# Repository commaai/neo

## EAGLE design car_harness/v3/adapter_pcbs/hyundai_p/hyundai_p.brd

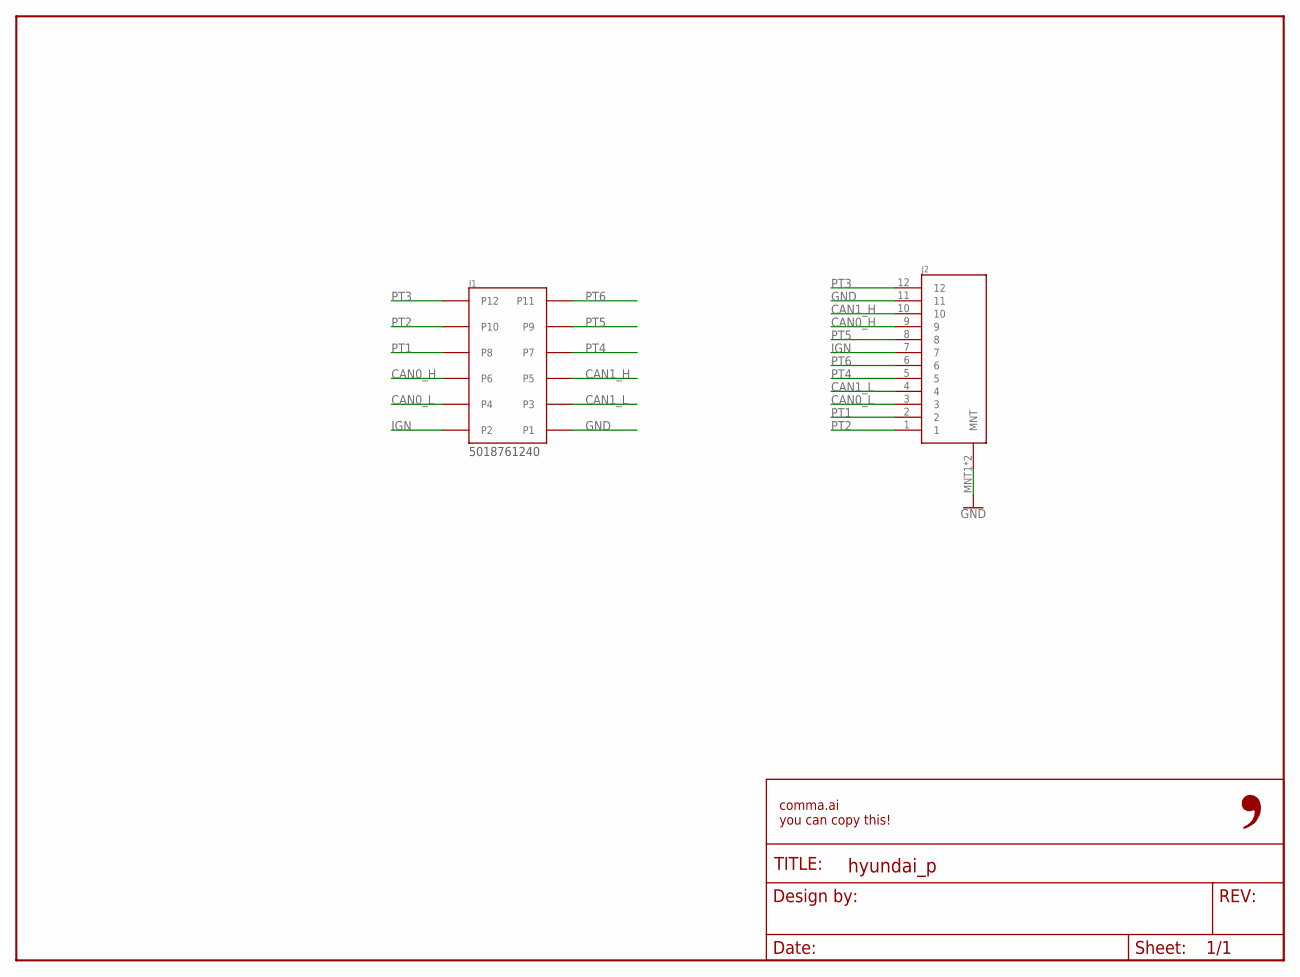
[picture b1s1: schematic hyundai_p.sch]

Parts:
FRAME1: FRAME-LETTER-OPENNO_PACKAGE; DUMMY
J1: 5018761240
J2: MG646151

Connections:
CAN0_H: J1.P6, J2.9
CAN0_L: J1.P4, J2.3
CAN1_H: J1.P5, J2.10
CAN1_L: J1.P3, J2.4
GND: J1.P1, J2.11, J2.MNT1 (MNT), J2.MNT2 (MNT)
IGN: J1.P2, J2.7
PT1: J1.P8, J2.2
PT2: J1.P10, J2.1
PT3: J1.P12, J2.12
PT4: J1.P7, J2.5
PT5: J1.P9, J2.8
PT6: J1.P11, J2.6

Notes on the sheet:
5018761240

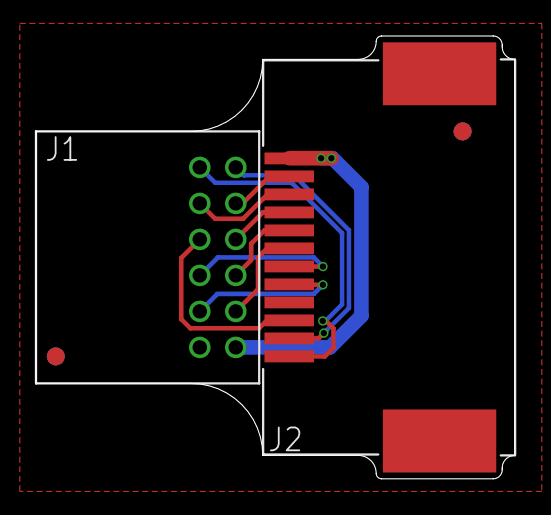
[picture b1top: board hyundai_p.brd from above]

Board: 2 copper layers, 26.6 x 24.6 mm, 6 parts (1 on the bottom side), 12 nets.

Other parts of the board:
U$1: LOGO
U$2, U$3: FIDUCIAL

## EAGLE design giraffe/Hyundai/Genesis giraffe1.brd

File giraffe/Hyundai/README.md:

thsi is test for hyundai Giraffe
the designs have not beeen tested

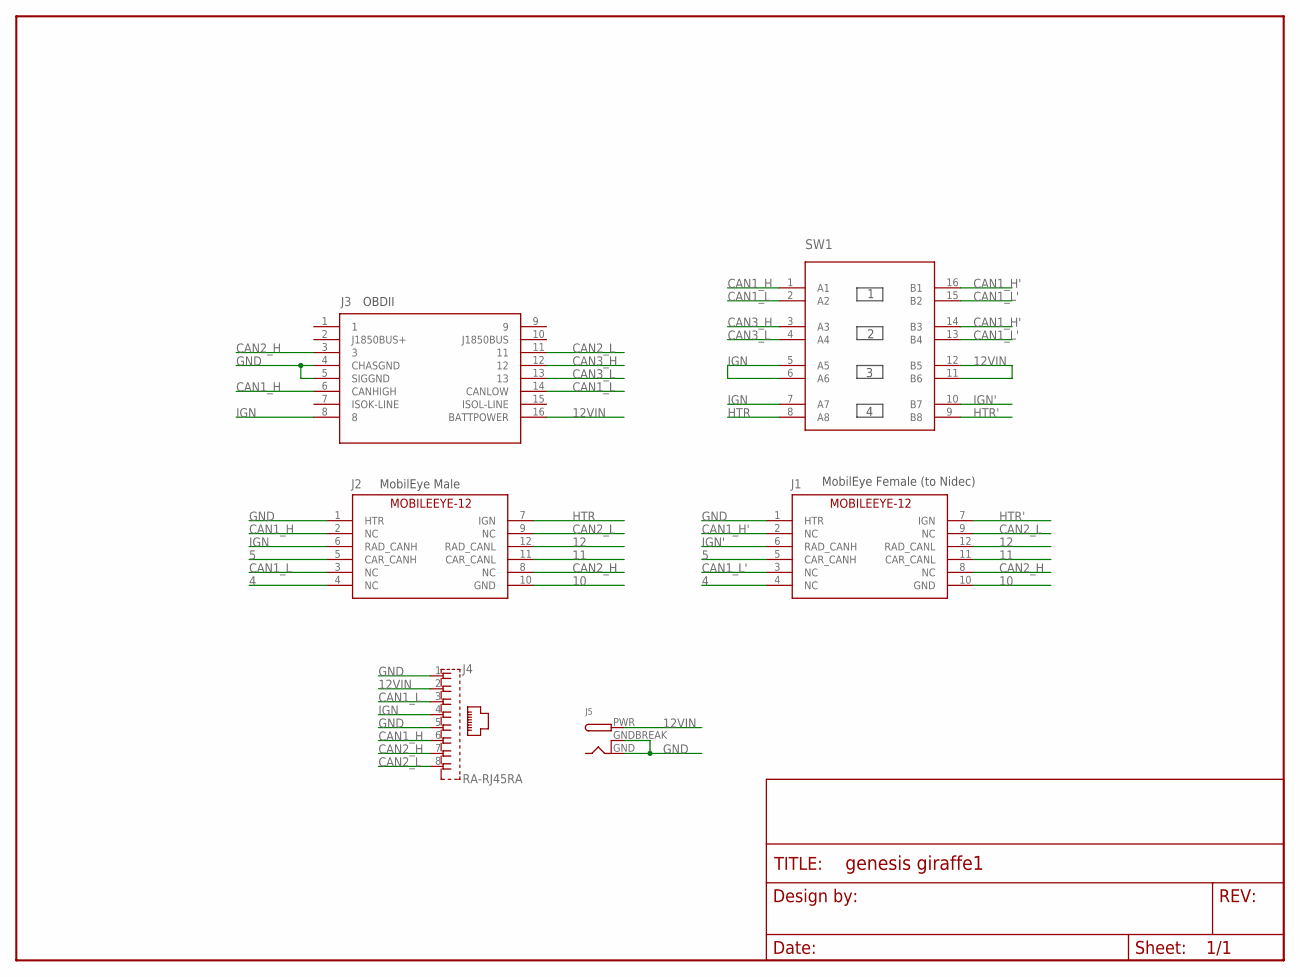
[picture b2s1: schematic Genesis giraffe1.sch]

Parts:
FRAME1: FRAME-LETTERNO_PACKAGE; DUMMY
J1: MOBILEEYE-12FEMALE; 2X6-TE-FEMALE
J2: MOBILEEYE-12MALE; 2X6-TE-RA
J3: OBDII-FEMALE-CUT; OBDII-FEMALE-MIDCUT
J4: RA-RJ45RA; RA-RJ45
J5: DCBARRELPTH; DCJACK_2MM_PTH
SW1: 4XDPSTSMT; 4-DPST

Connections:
4: J1.4 (NC), J2.4 (NC)
5: J1.5 (CAR_CANH), J2.5 (CAR_CANH)
10: J1.10 (GND), J2.10 (GND)
11: J1.11 (CAR_CANL), J2.11 (CAR_CANL)
12: J1.12 (RAD_CANL), J2.12 (RAD_CANL)
12VIN: J3.16 (BATTPOWER), J4.2, J5.PWR, SW1.11 (B6), SW1.12 (B5)
CAN1_H: J2.2 (NC), J3.6 (CANHIGH), J4.6, SW1.1 (A1)
CAN1_H': J1.2 (NC), SW1.14 (B3), SW1.16 (B1)
CAN1_L: J2.3 (NC), J3.14 (CANLOW), J4.3, SW1.2 (A2)
CAN1_L': J1.3 (NC), SW1.13 (B4), SW1.15 (B2)
CAN2_H: J1.8 (NC), J2.8 (NC), J3.3, J4.7
CAN2_L: J1.9 (NC), J2.9 (NC), J3.11, J4.8
CAN3_H: J3.12, SW1.3 (A3)
CAN3_L: J3.13, SW1.4 (A4)
GND: J1.1 (HTR), J2.1 (HTR), J3.4 (CHASGND), J3.5 (SIGGND), J4.1, J4.5, J5.GND, J5.GNDBREAK
HTR: J2.7 (IGN), SW1.8 (A8)
HTR': J1.7 (IGN), SW1.9 (B8)
IGN: J2.6 (RAD_CANH), J3.8, J4.4, SW1.5 (A5), SW1.6 (A6), SW1.7 (A7)
IGN': J1.6 (RAD_CANH), SW1.10 (B7)

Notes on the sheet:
OBDII
MobilEye Male
MobilEye Female (to Nidec)

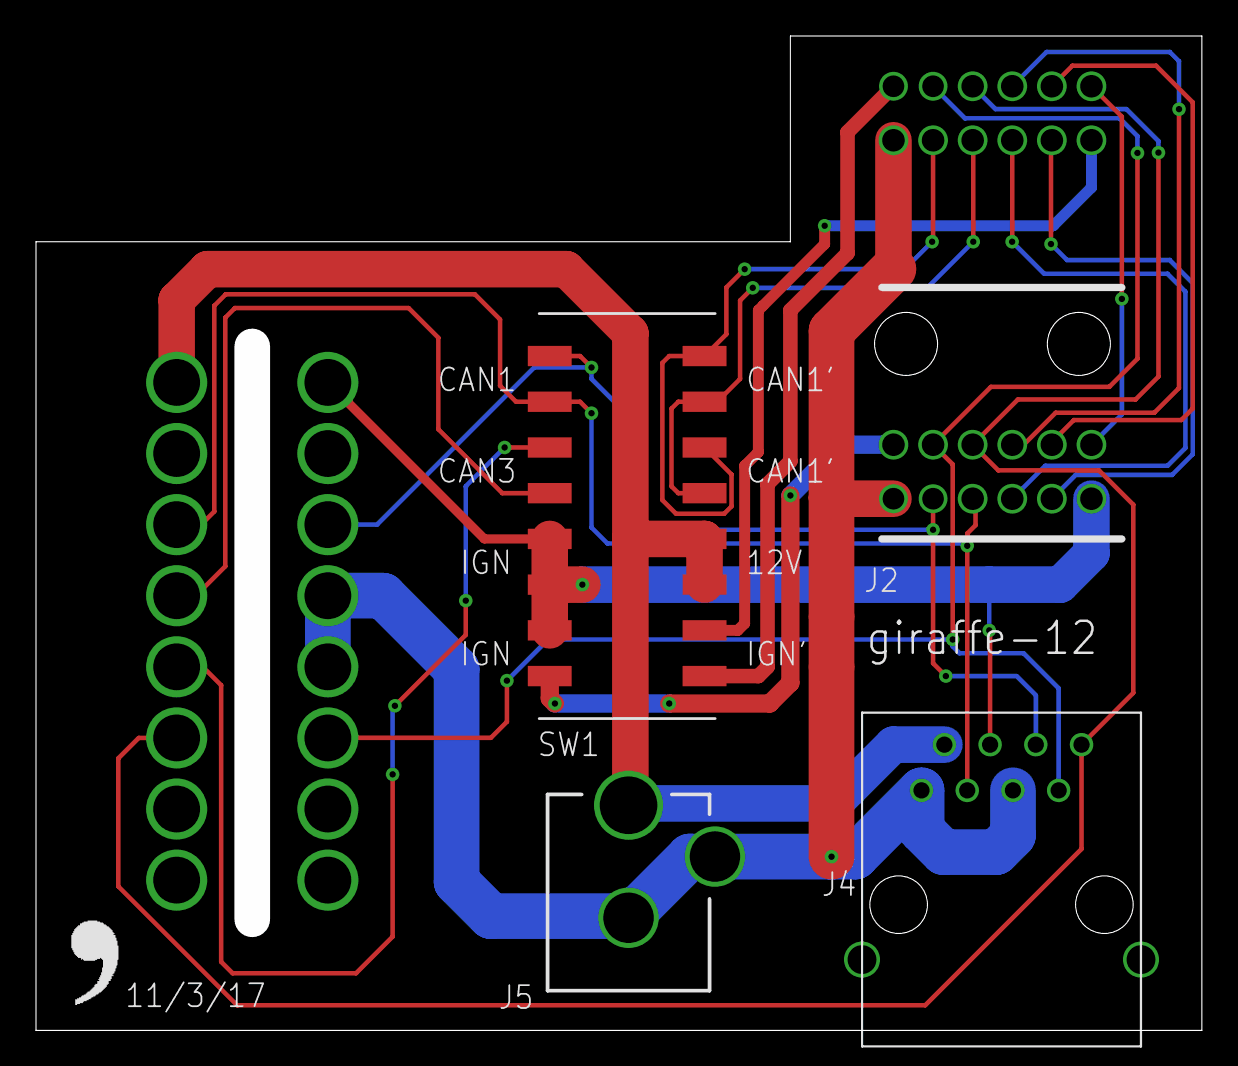
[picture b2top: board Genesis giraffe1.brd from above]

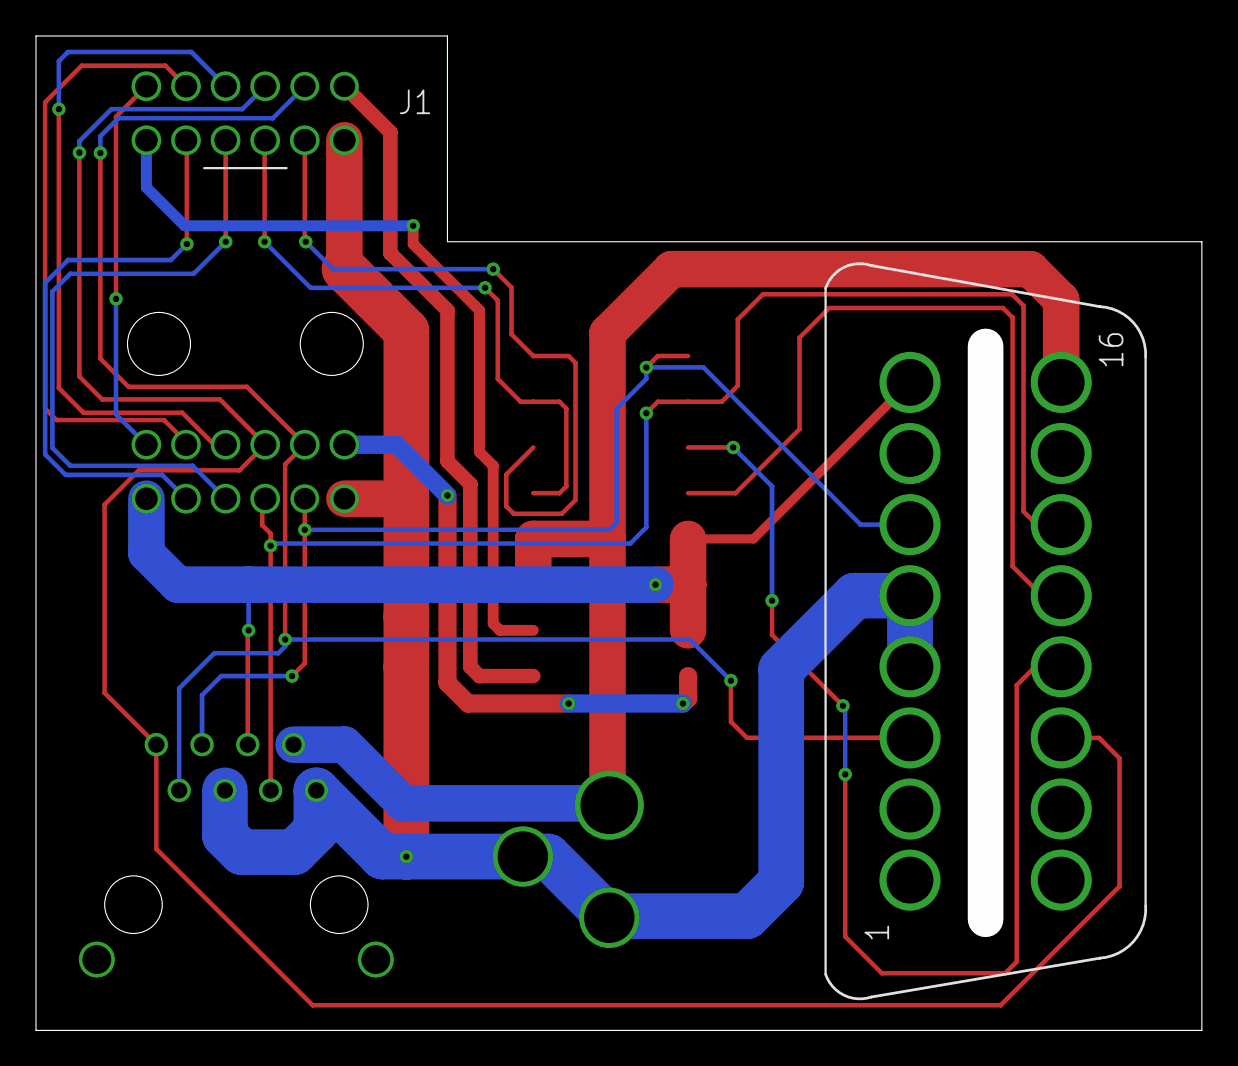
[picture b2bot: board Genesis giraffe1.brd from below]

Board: 2 copper layers, 64.8 x 55.2 mm, 8 parts (2 on the bottom side), 19 nets.

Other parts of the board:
U$1: LOGO

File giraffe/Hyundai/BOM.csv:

Ref Des,Package,Manufacturer PN,Qty,Link
J1,12-pin-RA,1318772-2,1,http://www.mouser.com/Search/ProductDetail.aspx?R=1318772-2v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
J2,12-pin,1318774-1,1,http://www.mouser.com/Search/ProductDetail.aspx?R=1318774-1v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
,,1123343-1,12,https://www.digikey.com/product-detail/en/te-connectivity-am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
,,PRPC040SAAN-RC,1,https://www.digikey.com/products/en?keywords=S1011EC-40-ND
J3,16-pin,OBDII-FEMALE,1,https://www.alibaba.com/product-detail/RIGHT-ANGLE-90-degree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
J4,RJ45-RA,A-2004-2-4-LPS-N-R,1,https://www.digikey.com/product-detail/en/assmann-wsw-compon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
J5,3-pin,EJ508A,1,https://www.digikey.com/products/en?keywords=ej508a
SW1,SMD,204-214ST,1,https://www.digikey.com/scripts/DkSearch/dksus.dll?Detail&it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
SCREWs,Phillips,92010A118,2,https://www.mcmaster.com/#catalog/92010A118

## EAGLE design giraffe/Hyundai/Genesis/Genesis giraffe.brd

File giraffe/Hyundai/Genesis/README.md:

this is for Genesis modefied from Toyoto giraffe
It has clearance issue if connected to Genesis, Panda would interfere with LKAS modul. the solution is 90 degree ObdII to replace the normal one.
https://www.alibaba.com/product-detail/RIGHT-ANGLE-90-degree-J1962-OBD_60710796767.html?spm=a2700.8443308.0.0.7eaa3e5fumKyTI

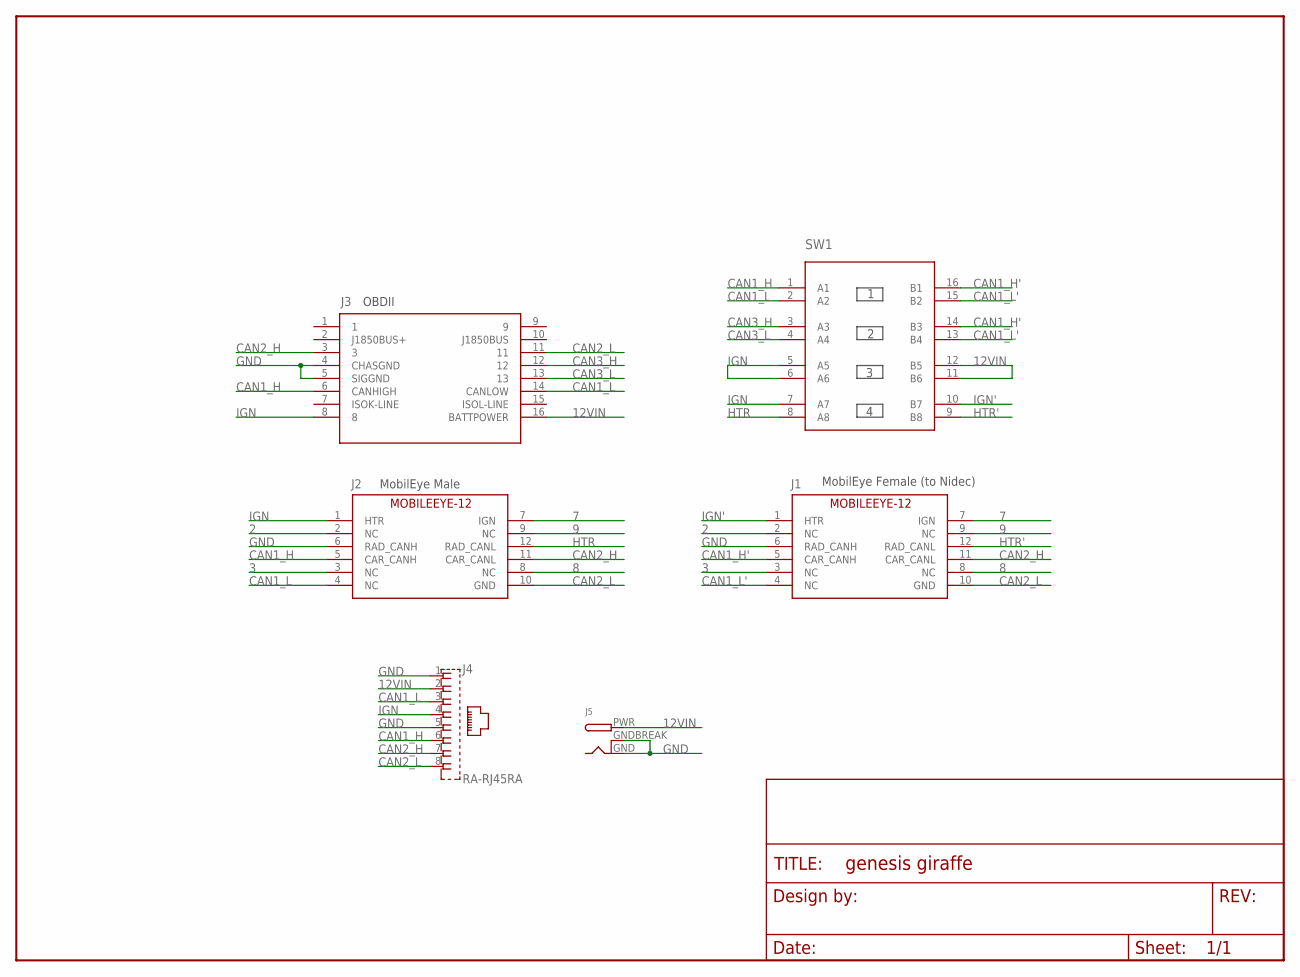
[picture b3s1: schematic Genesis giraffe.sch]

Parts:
FRAME1: FRAME-LETTERNO_PACKAGE; DUMMY
J1: MOBILEEYE-12FEMALE; 2X6-TE-FEMALE
J2: MOBILEEYE-12MALE; 2X6-TE-RA
J3: COMMA.AI_OBDII-FEMALE; COMMA.AI_2X6-TE-FEMALE_NEW1
J4: RA-RJ45RA; RA-RJ45
J5: DCBARRELPTH; DCJACK_2MM_PTH
SW1: 4XDPSTSMT; 4-DPST

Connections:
2: J1.2 (NC), J2.2 (NC)
3: J1.3 (NC), J2.3 (NC)
7: J1.7 (IGN), J2.7 (IGN)
8: J1.8 (NC), J2.8 (NC)
9: J1.9 (NC), J2.9 (NC)
12VIN: J3.16 (BATTPOWER), J4.2, J5.PWR, SW1.11 (B6), SW1.12 (B5)
CAN1_H: J2.5 (CAR_CANH), J3.6 (CANHIGH), J4.6, SW1.1 (A1)
CAN1_H': J1.5 (CAR_CANH), SW1.14 (B3), SW1.16 (B1)
CAN1_L: J2.4 (NC), J3.14 (CANLOW), J4.3, SW1.2 (A2)
CAN1_L': J1.4 (NC), SW1.13 (B4), SW1.15 (B2)
CAN2_H: J1.11 (CAR_CANL), J2.11 (CAR_CANL), J3.3, J4.7
CAN2_L: J1.10 (GND), J2.10 (GND), J3.11, J4.8
CAN3_H: J3.12, SW1.3 (A3)
CAN3_L: J3.13, SW1.4 (A4)
GND: J1.6 (RAD_CANH), J2.6 (RAD_CANH), J3.4 (CHASGND), J3.5 (SIGGND), J4.1, J4.5, J5.GND, J5.GNDBREAK
HTR: J2.12 (RAD_CANL), SW1.8 (A8)
HTR': J1.12 (RAD_CANL), SW1.9 (B8)
IGN: J2.1 (HTR), J3.8, J4.4, SW1.5 (A5), SW1.6 (A6), SW1.7 (A7)
IGN': J1.1 (HTR), SW1.10 (B7)

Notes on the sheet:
OBDII
MobilEye Male
MobilEye Female (to Nidec)

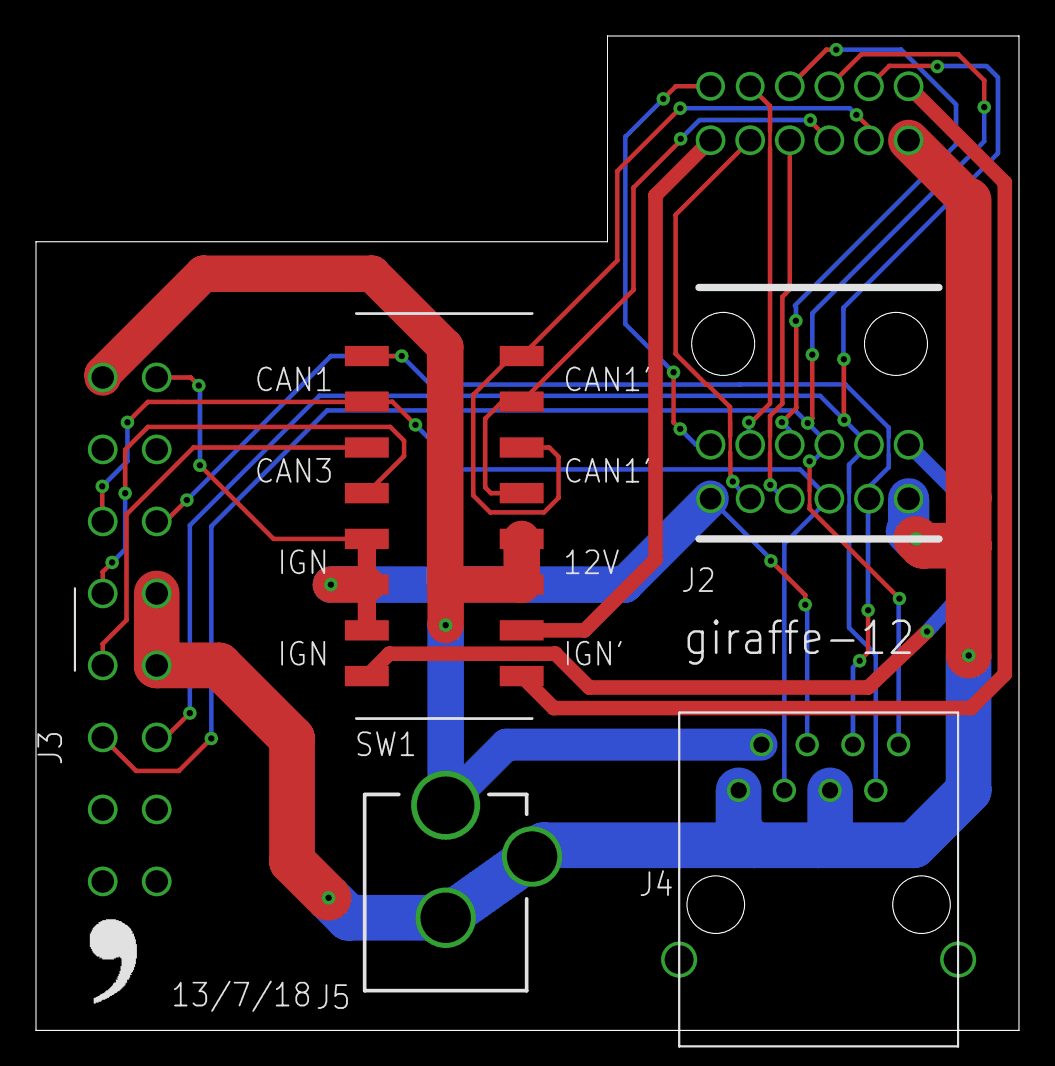
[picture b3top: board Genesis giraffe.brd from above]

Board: 2 copper layers, 54.6 x 55.2 mm, 8 parts (1 on the bottom side), 19 nets.

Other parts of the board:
U$1: LOGO

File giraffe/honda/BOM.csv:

Ref Des,Package,Manufacturer PN,Qty,Link
J1,20-pin-RA,MX34020NF1,1,https://www.digikey.com/product-detail/en/jae-electronics/MX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
J2,20-pin,MX34020SF1,1,https://www.digikey.com/product-detail/en/jae-electronics/MX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
,,M34S75C4F1,20,https://www.digikey.com/product-detail/en/jae-electronics/M3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
,,PRPC040SAAN-RC,1,https://www.digikey.com/product-detail/en/sullins-connector-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
J3,16-pin,OBDII-FEMALE,1,https://cn1514770021qfbj.en.alibaba.com/product/60598699808-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
J4,RJ45-VERT,A-2014-2-4-LP/FS-R,1,https://www.digikey.com/product-detail/en/assmann-wsw-compon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
SW1,SMD,204-214ST,1,https://www.digikey.com/product-detail/en/cts-electrocompone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
SCREWs,Phillips,92010A118,2,https://www.mcmaster.com/#catalog/92010A118

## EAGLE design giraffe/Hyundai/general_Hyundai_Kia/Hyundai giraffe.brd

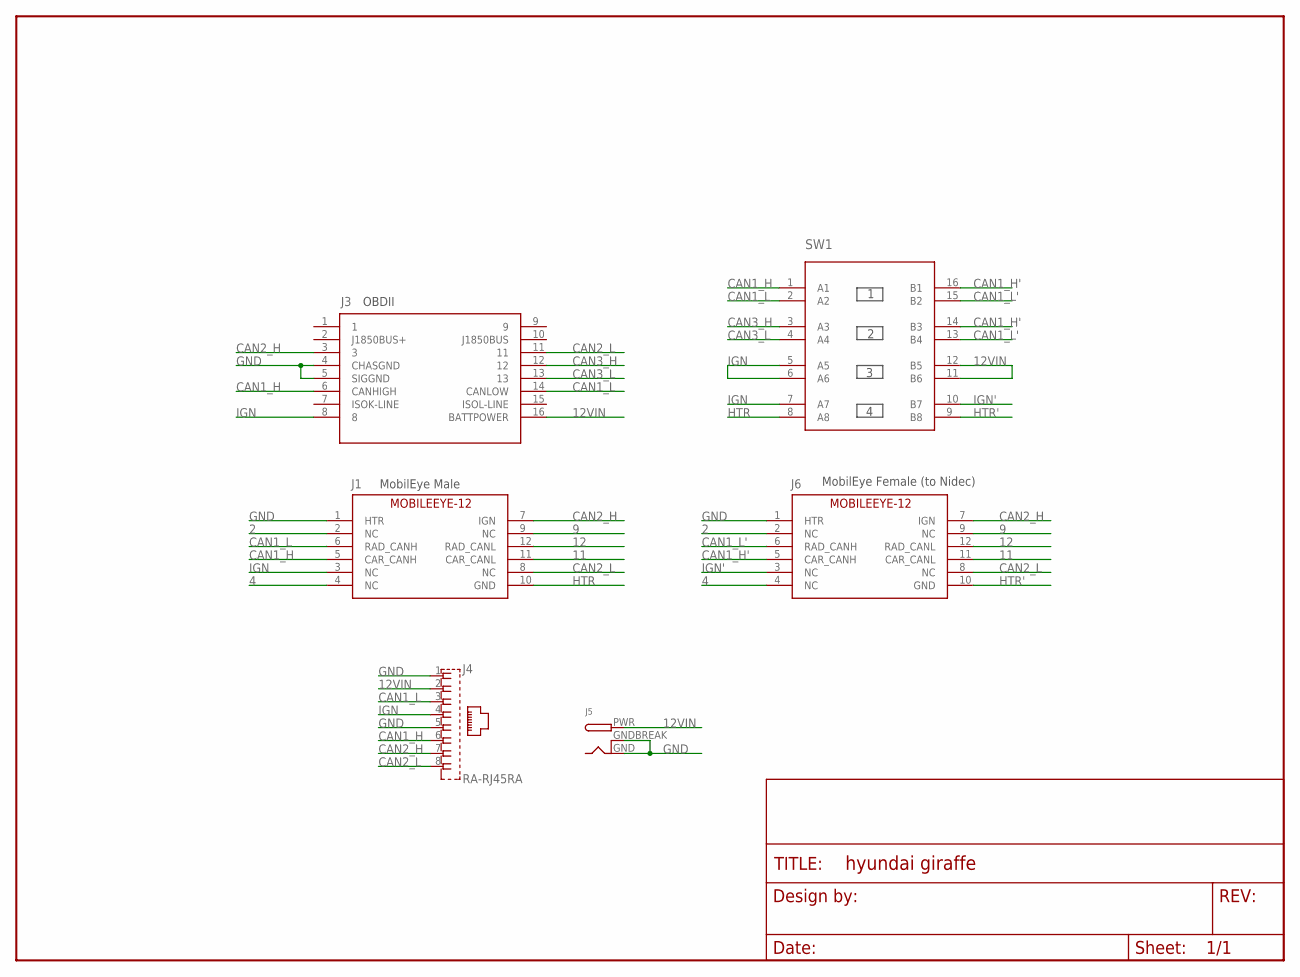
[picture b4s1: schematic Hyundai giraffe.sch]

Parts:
FRAME1: FRAME-LETTERNO_PACKAGE; DUMMY
J1: COMMA.AI_MOBILEEYE-12NEW; COMMA.AI_2X6-TE-RA_NEW
J3: OBDII-FEMALE-CUT; OBDII-FEMALE-MIDCUT
J4: RA-RJ45RA; RA-RJ45
J5: DCBARRELPTH; DCJACK_2MM_PTH
J6: COMMA.AI_MOBILEEYE-12; COMMA.AI_2X6-TE-FEMALE_NEW
SW1: 4XDPSTSMT; 4-DPST

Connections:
2: J1.2 (NC), J6.2 (NC)
4: J1.4 (NC), J6.4 (NC)
9: J1.9 (NC), J6.9 (NC)
11: J1.11 (CAR_CANL), J6.11 (CAR_CANL)
12: J1.12 (RAD_CANL), J6.12 (RAD_CANL)
12VIN: J3.16 (BATTPOWER), J4.2, J5.PWR, SW1.11 (B6), SW1.12 (B5)
CAN1_H: J1.5 (CAR_CANH), J3.6 (CANHIGH), J4.6, SW1.1 (A1)
CAN1_H': J6.5 (CAR_CANH), SW1.14 (B3), SW1.16 (B1)
CAN1_L: J1.6 (RAD_CANH), J3.14 (CANLOW), J4.3, SW1.2 (A2)
CAN1_L': J6.6 (RAD_CANH), SW1.13 (B4), SW1.15 (B2)
CAN2_H: J1.7 (IGN), J3.3, J4.7, J6.7 (IGN)
CAN2_L: J1.8 (NC), J3.11, J4.8, J6.8 (NC)
CAN3_H: J3.12, SW1.3 (A3)
CAN3_L: J3.13, SW1.4 (A4)
GND: J1.1 (HTR), J3.4 (CHASGND), J3.5 (SIGGND), J4.1, J4.5, J5.GND, J5.GNDBREAK, J6.1 (HTR)
HTR: J1.10 (GND), SW1.8 (A8)
HTR': J6.10 (GND), SW1.9 (B8)
IGN: J1.3 (NC), J3.8, J4.4, SW1.5 (A5), SW1.6 (A6), SW1.7 (A7)
IGN': J6.3 (NC), SW1.10 (B7)

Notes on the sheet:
OBDII
MobilEye Male
MobilEye Female (to Nidec)

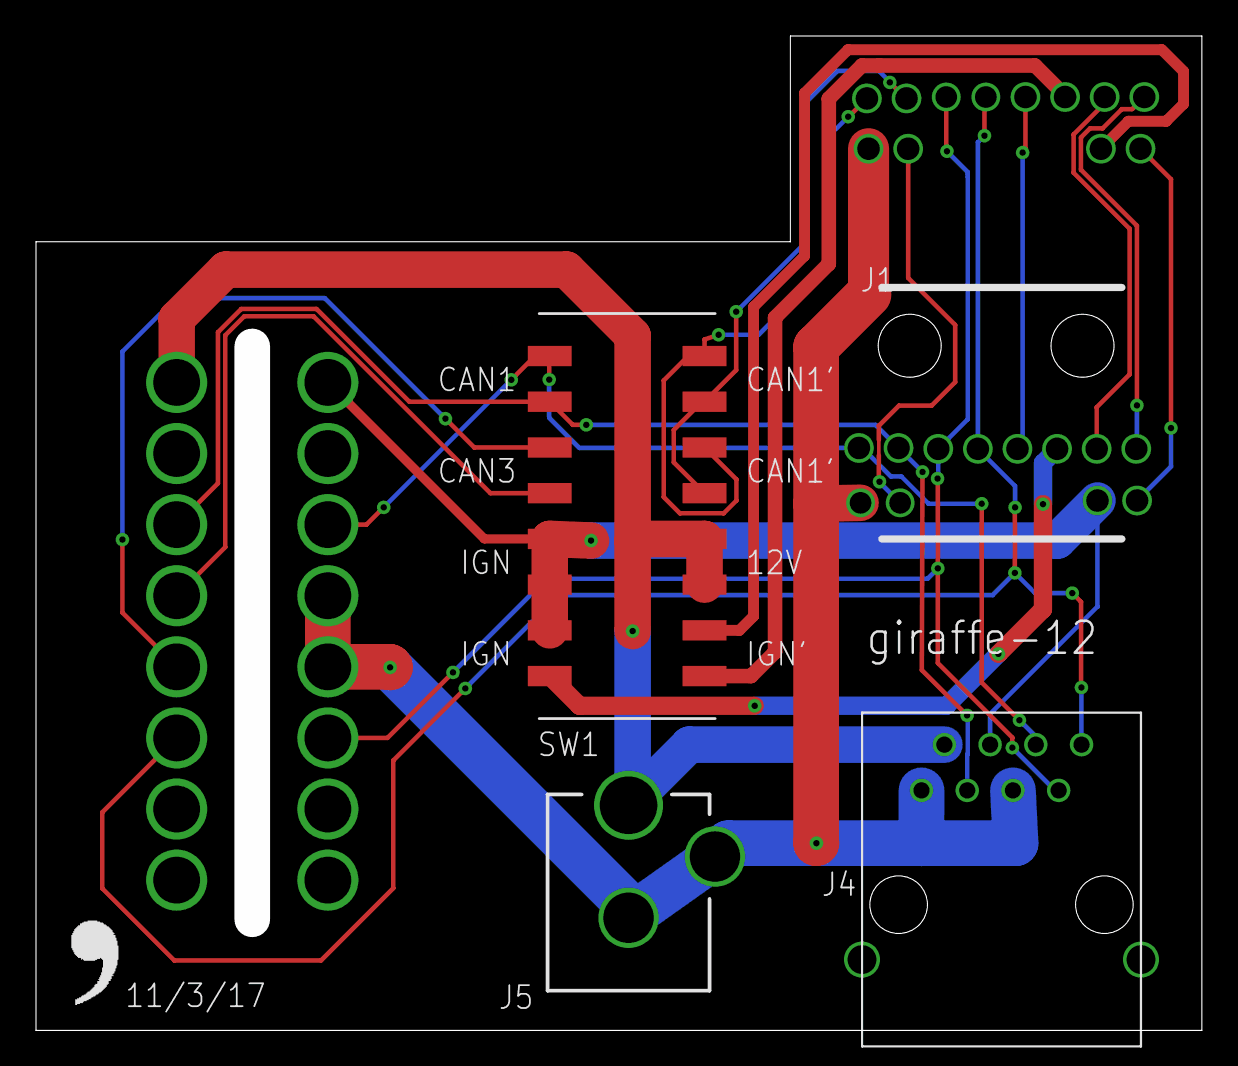
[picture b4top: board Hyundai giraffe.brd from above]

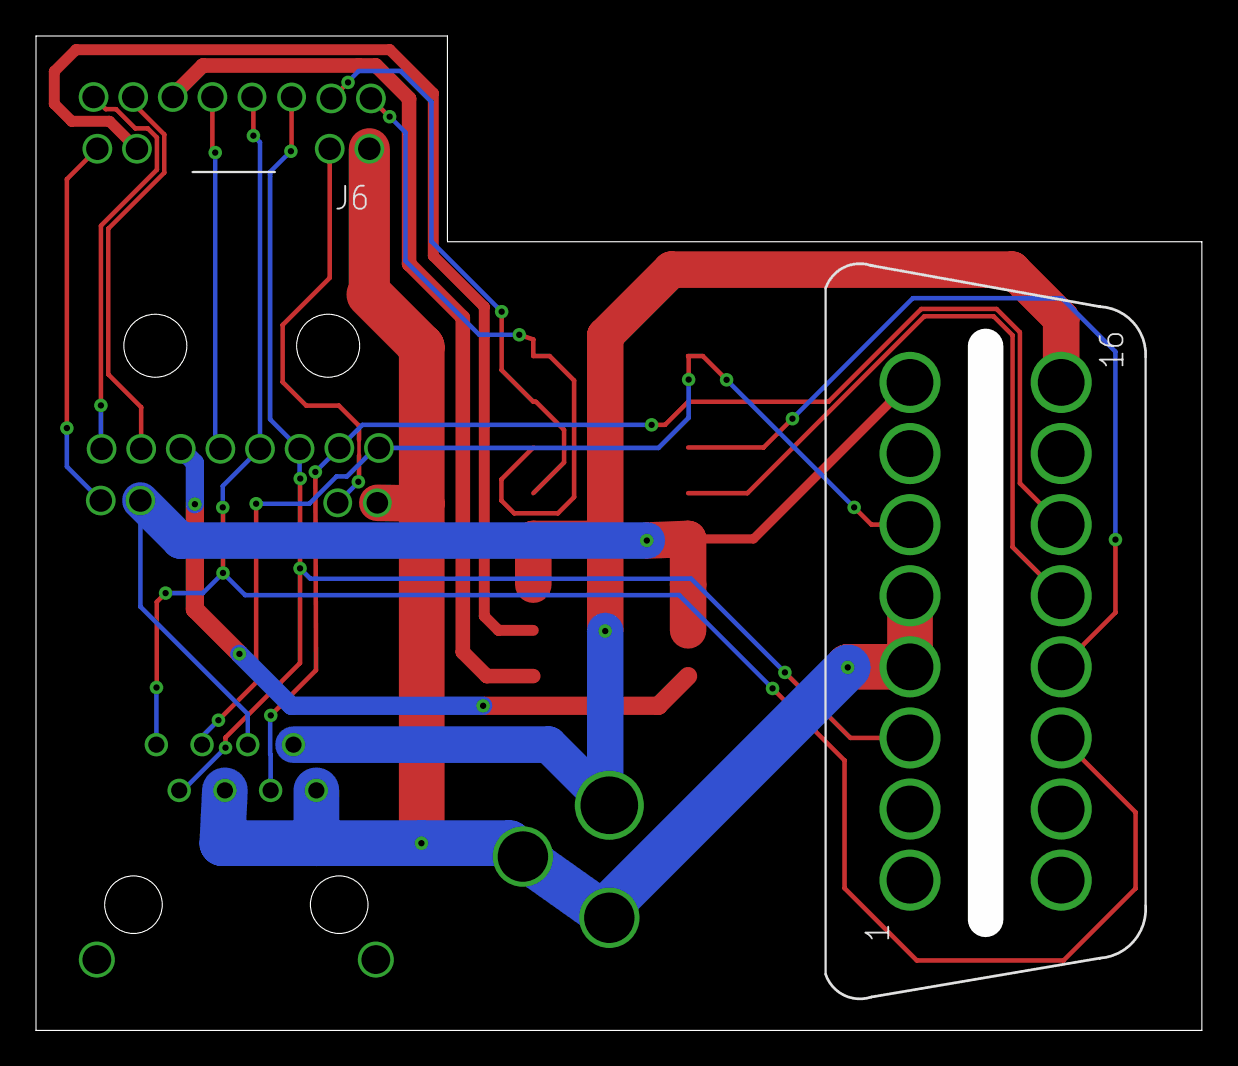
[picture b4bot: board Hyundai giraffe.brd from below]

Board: 2 copper layers, 64.8 x 55.2 mm, 8 parts (2 on the bottom side), 19 nets.

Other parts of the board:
U$1: LOGO

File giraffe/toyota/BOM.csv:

Ref Des,Package,Manufacturer PN,Qty,Link
J1,12-pin-RA,1318772-2,1,http://www.mouser.com/Search/ProductDetail.aspx?R=1318772-2v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
J2,12-pin,1318774-1,1,http://www.mouser.com/Search/ProductDetail.aspx?R=1318774-1v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
,,1123343-1,12,https://www.digikey.com/product-detail/en/te-connectivity-am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
,,PRPC040SAAN-RC,1,https://www.digikey.com/products/en?keywords=S1011EC-40-ND
J3,16-pin,OBDII-FEMALE,1,https://cn1514770021qfbj.en.alibaba.com/product/60598699808-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
J4,RJ45-RA,A-2004-2-4-LPS-N-R,1,https://www.digikey.com/product-detail/en/assmann-wsw-compon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
J5,3-pin,EJ508A,1,https://www.digikey.com/products/en?keywords=ej508a
SW1,SMD,204-214ST,1,https://www.digikey.com/scripts/DkSearch/dksus.dll?Detail&it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
SCREWs,Phillips,92010A118,2,https://www.mcmaster.com/#catalog/92010A118
,,,,
,,,,
,,,,
,,,,
,,,,
,,,,
,,,,
,,,,
,,,,EJ508A

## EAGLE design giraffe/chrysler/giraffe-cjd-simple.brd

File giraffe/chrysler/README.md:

Chrysler, Jeep, and Dodge use Mini50 unsealed 12-circuit (12CKT) Molex connectors.
The Vertical Header (VHDR) is the part that the car's canbus connects to. It's this part: https://www.digikey.com/product-detail/en/molex-llc/0348250124/WM10326-ND/4504599
with this set of dimentions: https://www.molex.com/pdm_docs/sd/348250124_sd.pdf

Going to the stock-LKAS camera is a receptacle (CONN RCPT) which has the same dimensions as the vertical header.
This is the receptacle: https://www.digikey.com/product-detail/en/molex-llc/0348240124/WM10324-ND/4504597
and you'll need these crimp terminals to put wires (or headers) into the receptacle: https://www.molex.com/molex/products/datasheet.jsp?part=active/5600230448_CRIMP_TERMINALS.xml
The receptacle does not have any post holes, but I left them in the PCB design so I could reuse the same part in Eagle as the header.

The work is based on a Chrysler Pacifica Hybrid 2017, although others appear to be the same.

Here is the pin-out for the forward-facing camera as supplied by Mopar (Chrysler): http://connectors.dcctools.com/details.htm?id=203000

## Parts list (BOM)
* RJ45 jack for future EON/Pandas that use RJ45 instead of OBD2: RJ45-RA	A-2004-2-4-LPS-N-R	1	https://www.digikey.com/product-detail/en/assmann-wsw-components/A-2004-2-4-LPS-N-R/AE10387-ND/2183638
* Power barrel connector to provide 12V from your Comma Power (can avoid this by wiring IGN to 12V and not using Comma Power): 3-pin	EJ508A	1	https://www.digikey.com/products/en?keywords=ej508a
* Switch to choose stock camera signals: SMD	204-214ST	1 https://www.digikey.com/product-detail/en/cts-electrocomponents/204-214ST/CT204214ST-ND/267313
* OBD2 connector for the Panda to plug in: 16-pin	OBDII-FEMALE	1	https://cn1514770021qfbj.en.alibaba.com/product/60598699808-804284542/J1962F_OBD2_16_Pin_Female_connector_OBD2_Socket.html
* 6 or more generic headers or stiff wire that will go in the terminals: https://www.digikey.com/products/en?keywords=S1011EC-40-ND (This linked item is 40 headers together, so you only need to buy one.)
* Mini50 vertical header: Molex 0348250124 WM10326-ND https://www.digikey.com/product-detail/en/molex-llc/0348250124/WM10326-ND/4504599
* Mini50 receptacle: Molex 0348240124 WM10324-ND https://www.digikey.com/product-detail/en/molex-llc/0348240124/WM10324-ND/4504597
  * If out of stock, the bridge version will work but won't sit flush on the PCB: 0348241124 https://www.digikey.com/product-detail/en/molex-llc/0348241124/WM13165-ND/4693133
* 6 or more Mini50 terminal connectors to put the headers into the receptacle: Molex 5600230448 WM16315CT-ND https://www.digikey.com/product-detail/en/molex-llc/5600230448/WM16315CT-ND/6702303
  * There are several different types of terminals. Pretty much any of them should work. The sizes are for different gage of wires: L for 0.35mm2, M for 0.22mm2, S for 0.13mm2. The linked headers are 0.41mm2, so get the L size, which is what I've linked to here.

## Troubleshooting

If you get a wire incorrect and the car starts faulting, typically removing your hardware and then turning the car off and back on again will fix it. If you can't turn the car off, such as due to faulting the shifter, then there are fuses located in the engine compartment, under the battery's black plastic cover. Carefully pull the fuse, check if it's blown and replace it. Warning: electricity can kill or injure you, refer to your car's service manual. The map for which fuse is which is located on the inside of the black plastic cover that you need to remove to access the fuses. Try removing and replacing these fuses to reboot the car (for 2017 pacifica hybrid):
- F78 is blue 15A (shifter)
- F57 (PIM - Main Power Supply)
- F62 (PIM - Redundant Main Power Supply)

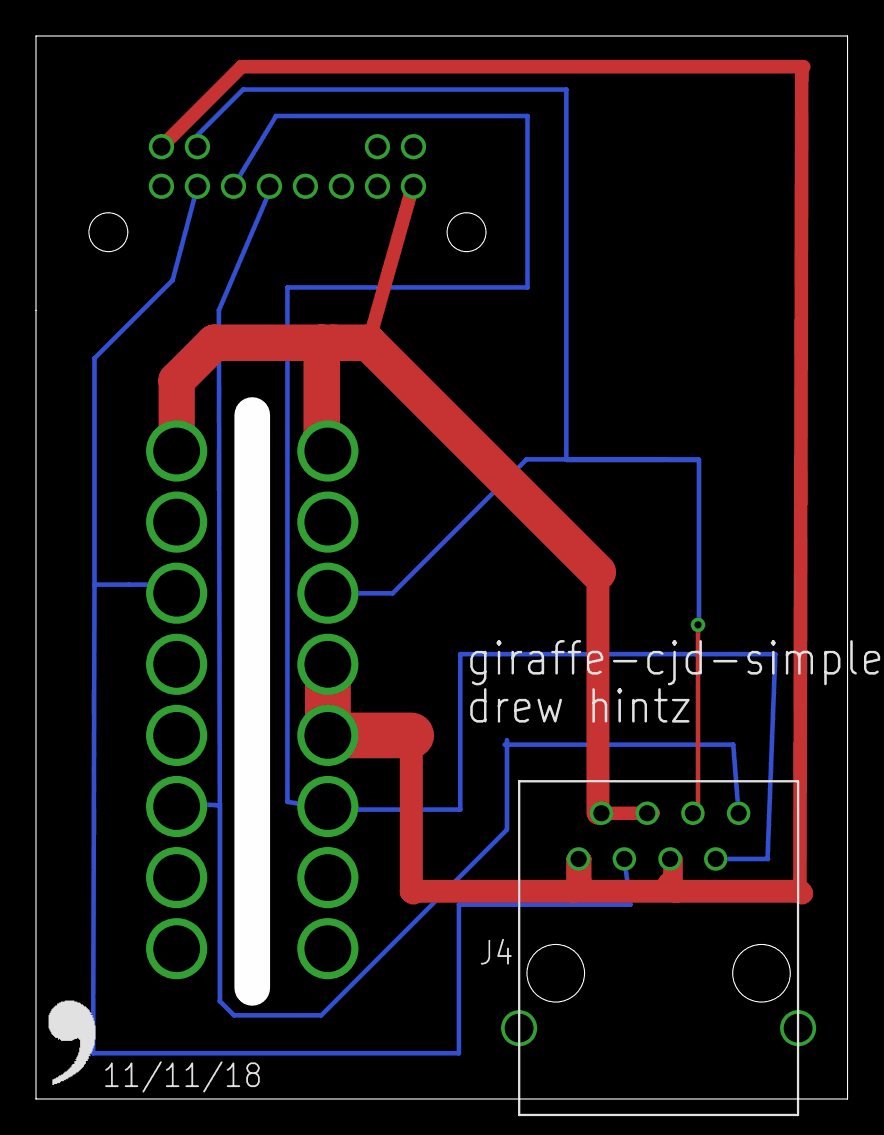
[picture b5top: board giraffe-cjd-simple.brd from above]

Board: 2 copper layers, 45.1 x 59.1 mm, 5 parts (1 on the bottom side), 3 nets.

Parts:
FRAME1: FRAME-LETTERNO_PACKAGE; DUMMY
J2: MINI50-12
J3: OBDII-FEMALE-CUT; OBDII-FEMALE-MIDCUT
J4: RA-RJ45RA; RA-RJ45
U$1: LOGO

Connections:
CAN1_L: J2.6, J4.3
unnamed: J4.1, J4.5
unnamed: J3.4, J3.5

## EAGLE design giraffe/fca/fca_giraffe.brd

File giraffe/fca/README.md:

FCA (Fiat Chrysler Automotive) Giraffe
====

Get your panda deeper into your:

- 2017 Chrysler Pacifica Hybrid

May fit other FCA cars as well.

The switches
====

The 2 DIP switches control signals to the stock ADAS system

- 1 -- IGN to camera

- 2 -- ADAS CAN1 -> camera CAN (OBDII pins 12 & 13)

Initial design from the community from: [@adhintz](https://github.com/adhintz)

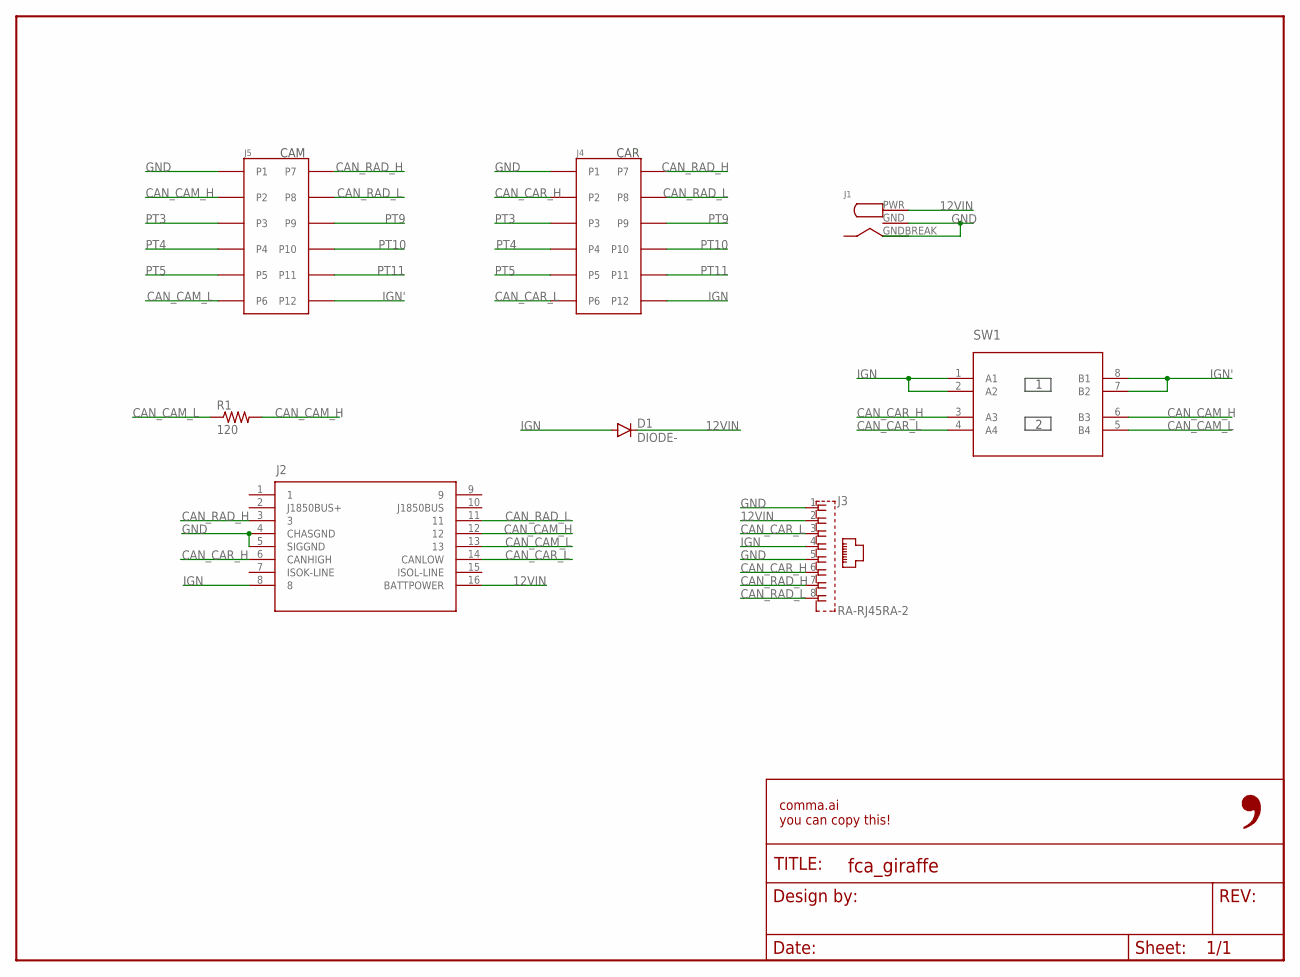
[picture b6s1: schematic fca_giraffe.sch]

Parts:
D1: DIODE-; DO-214
FRAME1: FRAME-LETTER-OPENNO_PACKAGE; DUMMY
J1: RASM722PX
J2: OBDII-FEMALE-CUT; OBDII-FEMALE-MIDCUT
J3: RA-RJ45RA-2; RA-RJ45-2
J4: 0348250124
J5: 0348240124
R1: 120; 0603-R
SW1: 2XDPST-CTS; 2-DPST

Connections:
12VIN: D1.1 (C), J1.PWR (12VIN), J2.16 (BATTPOWER), J3.2
CAN_CAM_H: J2.12, J5.P2, R1.2, SW1.6 (B3)
CAN_CAM_L: J2.13, J5.P6, R1.1, SW1.5 (B4)
CAN_CAR_H: J2.6 (CANHIGH), J3.6, J4.P2, SW1.3 (A3)
CAN_CAR_L: J2.14 (CANLOW), J3.3, J4.P6, SW1.4 (A4)
CAN_RAD_H: J2.3, J3.7, J4.P7, J5.P7
CAN_RAD_L: J2.11, J3.8, J4.P8, J5.P8
GND: J1.GND, J1.GNDBREAK, J2.4 (CHASGND), J2.5 (SIGGND), J3.1, J3.5, J4.P1, J5.P1
IGN: D1.2 (A), J2.8, J3.4, J4.P12, SW1.1 (A1), SW1.2 (A2)
IGN': J5.P12, SW1.7 (B2), SW1.8 (B1)
PT3: J4.P3, J5.P3
PT4: J4.P4, J5.P4
PT5: J4.P5, J5.P5
PT9: J4.P9, J5.P9
PT10: J4.P10, J5.P10
PT11: J4.P11, J5.P11

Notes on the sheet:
CAR
CAM

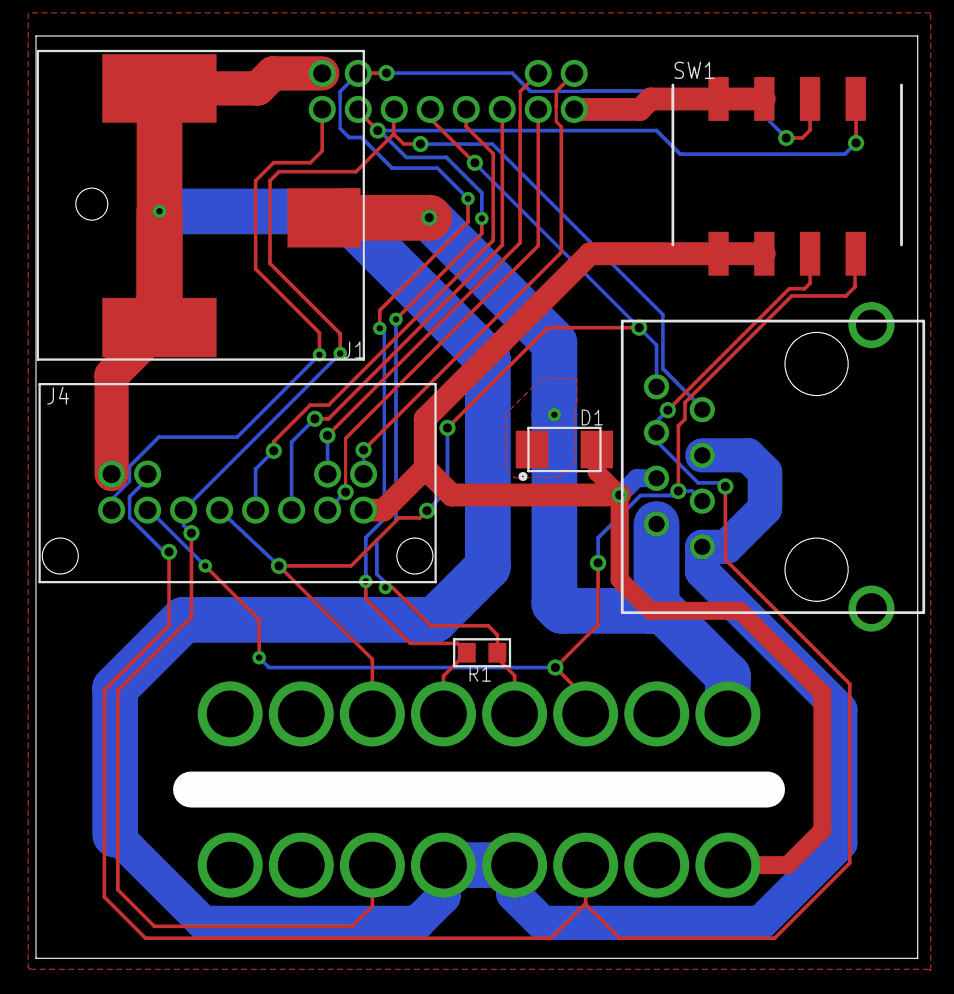
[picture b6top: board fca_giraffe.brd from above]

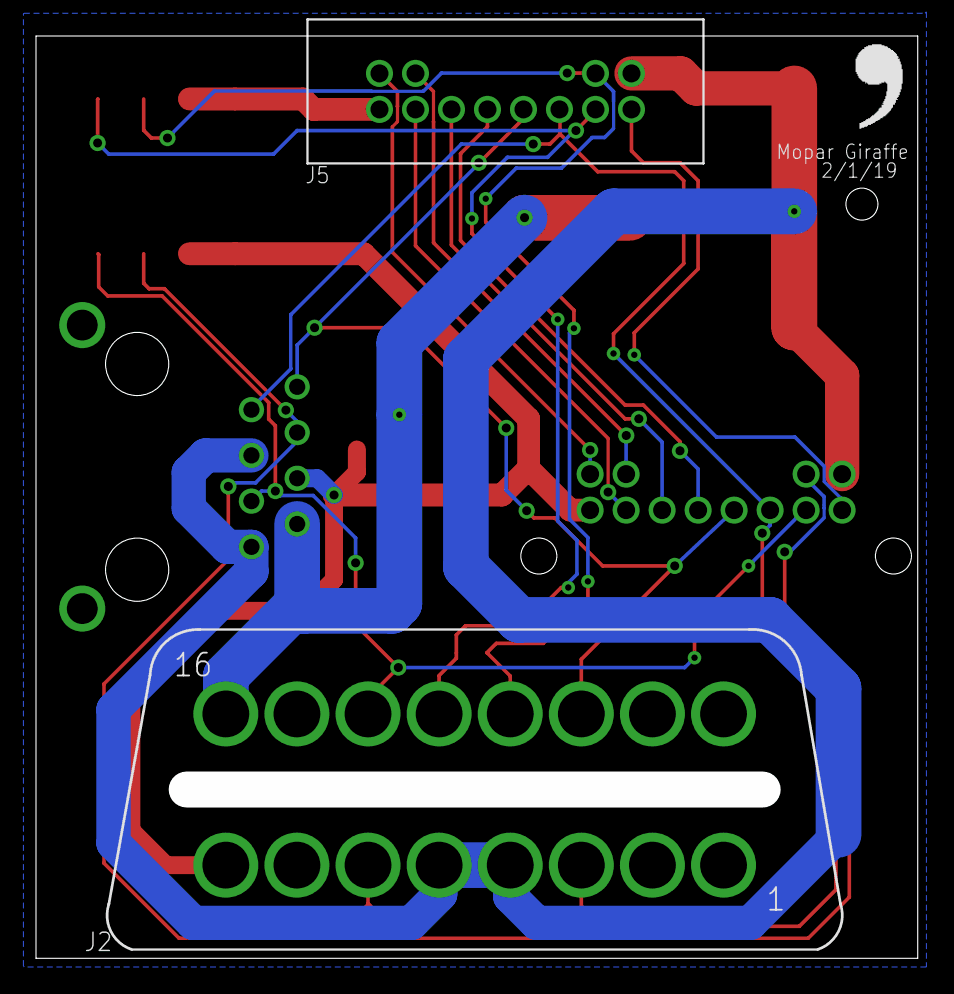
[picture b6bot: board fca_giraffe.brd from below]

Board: 2 copper layers, 49.0 x 51.2 mm, 10 parts (3 on the bottom side), 16 nets.

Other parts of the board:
U$1: LOGO

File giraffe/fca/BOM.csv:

Ref Des,Package,MPN,Qty,Link
J1,3-pin,RASM722PX,1,https://www.digikey.com/products/en?keywords=RASM722PX
J2,OBDII,,1,https://www.digikey.com/products/en?mpart=204-212ST&v=119
J3,RJ45-RA,A-2004-2-4-LPS-N-R,1,https://www.digikey.com/product-detail/en/assmann-wsw-compon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
J4,CONN HEADER VERT,348250124,1,https://www.digikey.com/product-detail/en/0348250124/WM10326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
J5,MINI50 CONN RCPT,348240124,1,https://www.digikey.com/product-detail/en/molex-llc/03482401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
SW1,SMD,CT204212ST-ND,1,https://www.digikey.com/products/en?mpart=204-212ST&v=119
D1,SMD,ES2BA-13-F,1,https://www.digikey.com/product-detail/en/diodes-incorporate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
R1, 0603R,ERJ-PA3J121V,1,https://www.digikey.com/product-detail/en/molex-llc/56002304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
Pins,,5600230421,12,https://www.digikey.com/product-detail/en/molex-llc/56002304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

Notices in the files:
parts and their libraries:
SparkFun-Aesthetics: Licensing: Creative Commons ShareAlike 4.0 International - https://creativecommons.org/licenses/by-sa/4.0
SparkFun-Aesthetics: Released under the Creative Commons Attribution Share-Alike 4.0 License
SparkFun-Aesthetics: https://creativecommons.org/licenses/by-sa/4.0
